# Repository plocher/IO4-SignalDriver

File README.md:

# IO4-SignalDriver
## License: CERN Open Hardware Licence v1.2

IO4 Output adapter driver for a 2-head signal mast

Takes an IO4-Output and drives 2x 3-LED common Anode signal heads using a demultiplexor logic chip.

Designed in conjunction with Jay Beckham for his South Shore Lines layout

Circuit testing:
  * The board needs to share a common ground with the remote controller (CMRI SMINI...) as the RJ45 only carries control signals
  * Drive the board with 5V DC through the IO4 connection
  * Signal heads / LEDs are "common anode" - pin4 of the signal head connector is VCC, the "colors" pins are driven LOW to energize the LED.
  * All control lines are pulled up logically on the signal driver board.
  * The board can drive 2x signal heads, each with R, Y, G and DARK aspects
      * Control signals 1 & 2 and  3 & 4, each control one head:
          : 00 - Green
          : 01 - Yellow
          : 10 - Red
          : 11 - Dark
  * The discrete resistors set a safe limit on the current allowed to the LED, and the trimmer pots can be used to further adjust the brightness.
  * The exact value depends on the specific attributes of the LED variety being used - specifically the forward voltage drop across the device. This info is found in the data sheet for the LED in question, or can be found experimentally.
      * Example:  with a 5v supply and a LED that drops 2.2v, the resistor sees (5-2.2 = 2.8v).  If we wish to limit the max current to 15mA, we need a fixed resistor of (2.8v / 0.015 = ~180 ohms).  If we add a 500 ohn trimmer resistor, that lets us adjust the current from 15mA max to about 4mA min.  High efficiency LEDs might need even LESS current, so upping the fixed resistor to 470R or even 1K0 might be appropriate.

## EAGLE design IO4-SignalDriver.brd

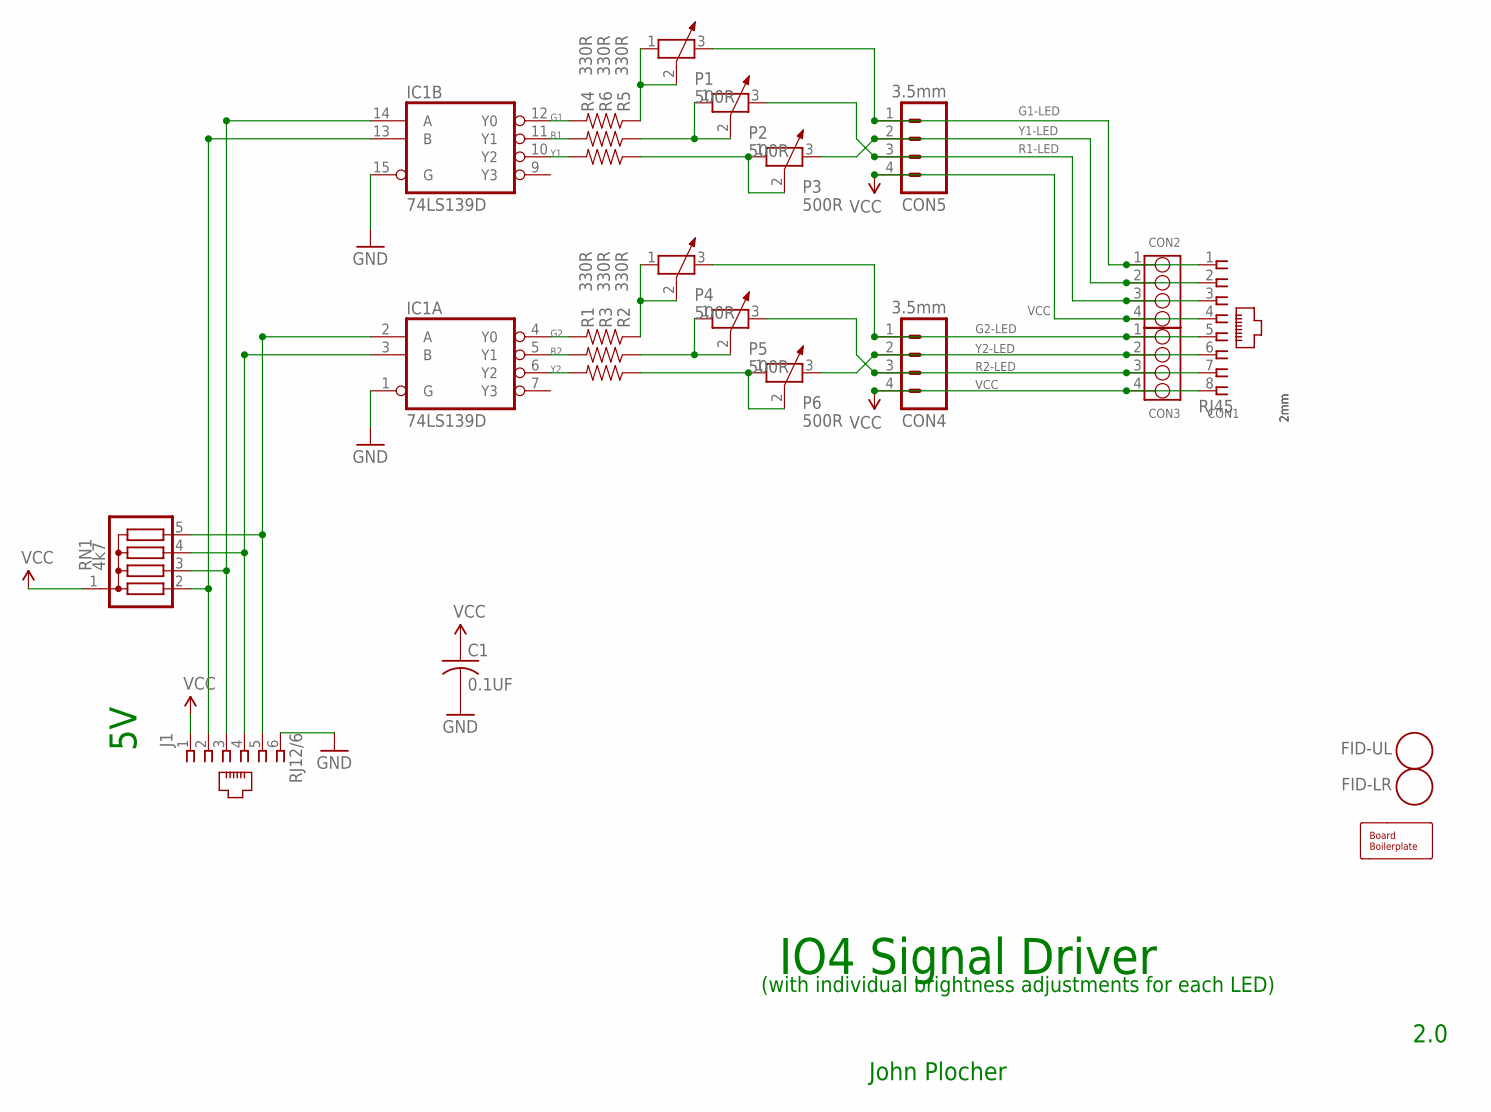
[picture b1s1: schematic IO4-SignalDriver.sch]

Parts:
BOARD1: BOARD; BOARD-DINRAIL-3.17INX10CM
C1: 0.1UF; 0603-CAP
CON1: RJ45; RJ45-NO-SHIELD
CON2, CON3: 2mm; 4P-2.0
CON4, CON5: 3.5mm; SCREWTERMINAL-3.5MM-4_LOCK
FID-LR: FIDUCIAL; FIDUCIAL_1MM
FID-UL: FIDUCIAL; FIDUCIAL_1MM
IC1: 74LS139D; SO16
J1: RJ12/6; RJ25-PANEL
P1, P2, P3, P4, P5, P6: 500R; P-3319
R1, R2, R3, R4, R5, R6: 330R; 0805-RES
RN1: 4k7; SIL5

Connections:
G1: IC1.12 (Y0), R4.2
G1-LED: CON1.1, CON2.1, CON5.1, P1.3
G1V: P1.1, P1.2, R4.1
G2: IC1.4 (Y0), R1.2
G2-LED: CON1.5, CON3.1, CON4.1, P4.3
G2V: P4.1, P4.2, R1.1
GND: C1.2, IC1.1 (G), IC1.8 (GND), IC1.15 (G), J1.6
unnamed: IC1.2 (A), J1.5, RN1.5
unnamed: IC1.3 (B), J1.4, RN1.4
unnamed: IC1.14 (A), J1.3, RN1.3
unnamed: IC1.13 (B), J1.2, RN1.2
R1: IC1.11 (Y1), R6.2
R1-LED: CON1.3, CON2.3, CON5.3, P2.3
R1V: P2.1, P2.2, R6.1
R2: IC1.5 (Y1), R3.2
R2-LED: CON1.7, CON3.3, CON4.3, P5.3
R2V: P5.1, P5.2, R3.1
VCC: C1.1, CON1.4, CON1.8, CON2.4, CON3.4, CON4.4, CON5.4, IC1.16 (VCC), J1.1, RN1.1
Y1: IC1.10 (Y2), R5.2
Y1-LED: CON1.2, CON2.2, CON5.2, P3.3
Y1V: P3.1, P3.2, R5.1
Y2: IC1.6 (Y2), R2.2
Y2-LED: CON1.6, CON3.2, CON4.2, P6.3
Y2V: P6.1, P6.2, R2.1

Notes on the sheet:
(with individual brightness adjustments for each LED)
John Plocher
2.0
IO4 Signal Driver

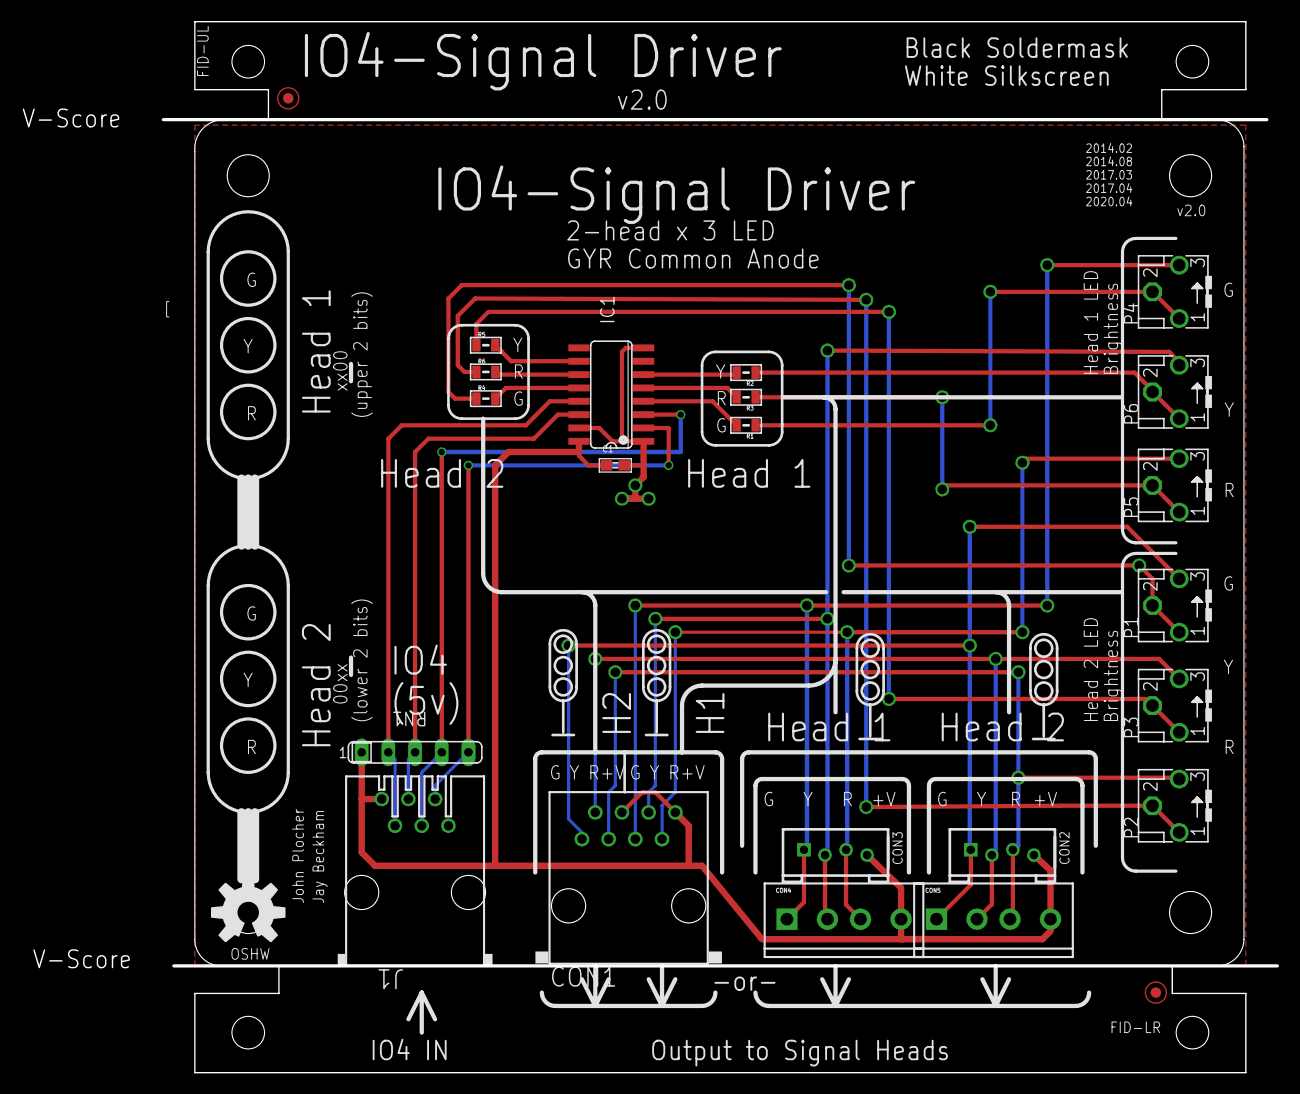
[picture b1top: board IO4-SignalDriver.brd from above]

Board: 2 copper layers, 119.4 x 99.8 mm, 25 parts (0 on the bottom side), 24 nets.

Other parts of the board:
U$2: OSHW; OSHW-LOGO-L

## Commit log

2020-04-26 Initial version
2020-04-26 convert to SMT, add 2mmx4 headers
2020-04-26 changed silkscreen version info
2020-04-26 removed unused sch sheet
2020-04-27 font=vector
2020-05-04 updated tags
2020-05-04 Not panelized
2020-08-12 Black soldermask
2020-08-12 FID placement & SPCoast update
2020-09-12 add graphic
2020-10-05 added values for connectors
2020-10-06 normalized values
